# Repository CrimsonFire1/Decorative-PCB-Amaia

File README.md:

# Decorative-PCB-Amaia
 Decorative PCB powered by Arduino Nano with LEDs (3 on-off, 3 capable of dimming), two piezo buzzers (play duets), and a button. Protective back is laser cut acrylic.

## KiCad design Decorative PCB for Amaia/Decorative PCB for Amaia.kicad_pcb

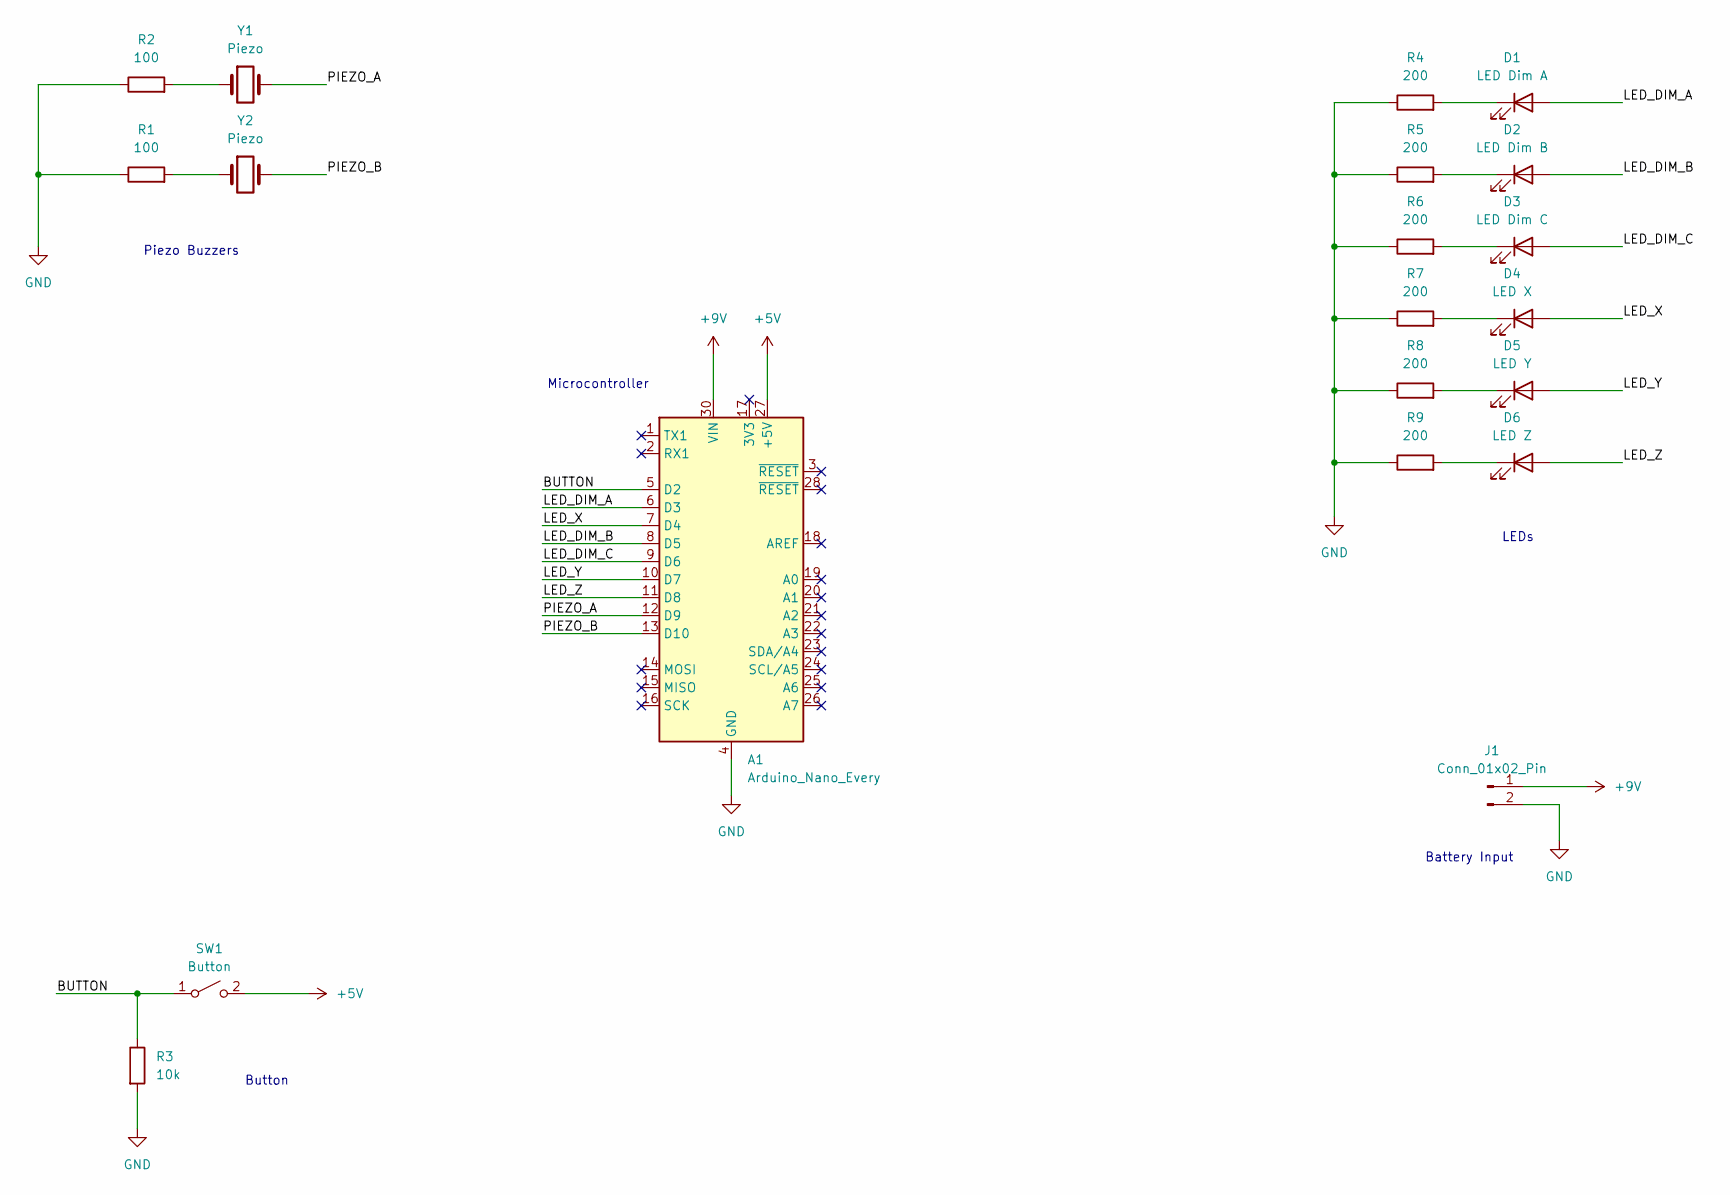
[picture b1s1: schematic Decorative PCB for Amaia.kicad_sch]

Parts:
A1: Arduino_Nano_Every; Nano_Every_Modified_Pads
D1: LED Dim A; LED_D5.0mm
D2: LED Dim B; LED_D5.0mm
D3: LED Dim C; LED_D5.0mm
D4: LED X; LED_D5.0mm
D5: LED Y; LED_D5.0mm
D6: LED Z; LED_D5.0mm
J1: Conn_01x02_Pin; SolderWire-0.5sqmm_1x02_P4.6mm_D0.9mm_OD2.1mm
R1, R2: 100; R_Axial_DIN0204_L3.6mm_D1.6mm_P7.62mm_Horizontal
R3: 10k; R_Axial_DIN0204_L3.6mm_D1.6mm_P7.62mm_Horizontal
R4, R5, R6, R7, R8, R9: 200; R_Axial_DIN0204_L3.6mm_D1.6mm_P7.62mm_Horizontal
SW1: Button; SW_PUSH_6mm
Y1, Y2: Piezo; Buzzer_Murata_PKMCS0909E

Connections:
+5V: A1.27 (+5V), SW1.2 (B)
+9V: A1.30 (VIN), J1.1
/BUTTON: A1.5 (D2), R3.1, SW1.1 (A)
/LED_DIM_A: A1.6 (D3), D1.2 (A)
/LED_DIM_B: A1.8 (D5), D2.2 (A)
/LED_DIM_C: A1.9 (D6), D3.2 (A)
/LED_X: A1.7 (D4), D4.2 (A)
/LED_Y: A1.10 (D7), D5.2 (A)
/LED_Z: A1.11 (D8), D6.2 (A)
/PIEZO_A: A1.12 (D9), Y1.2
/PIEZO_B: A1.13 (D10), Y2.2
GND: A1.4 (GND), A1.29 (GND), J1.2, R1.1, R2.1, R3.2, R4.1, R5.1, R6.1, R7.1, R8.1, R9.1
unnamed: D1.1 (K), R4.2
unnamed: D2.1 (K), R5.2
unnamed: D3.1 (K), R6.2
unnamed: D4.1 (K), R7.2
unnamed: D5.1 (K), R8.2
unnamed: D6.1 (K), R9.2
unnamed: R1.2, Y2.1
unnamed: R2.2, Y1.1

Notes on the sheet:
Battery Input
Button
Piezo Buzzers
Microcontroller
LEDs

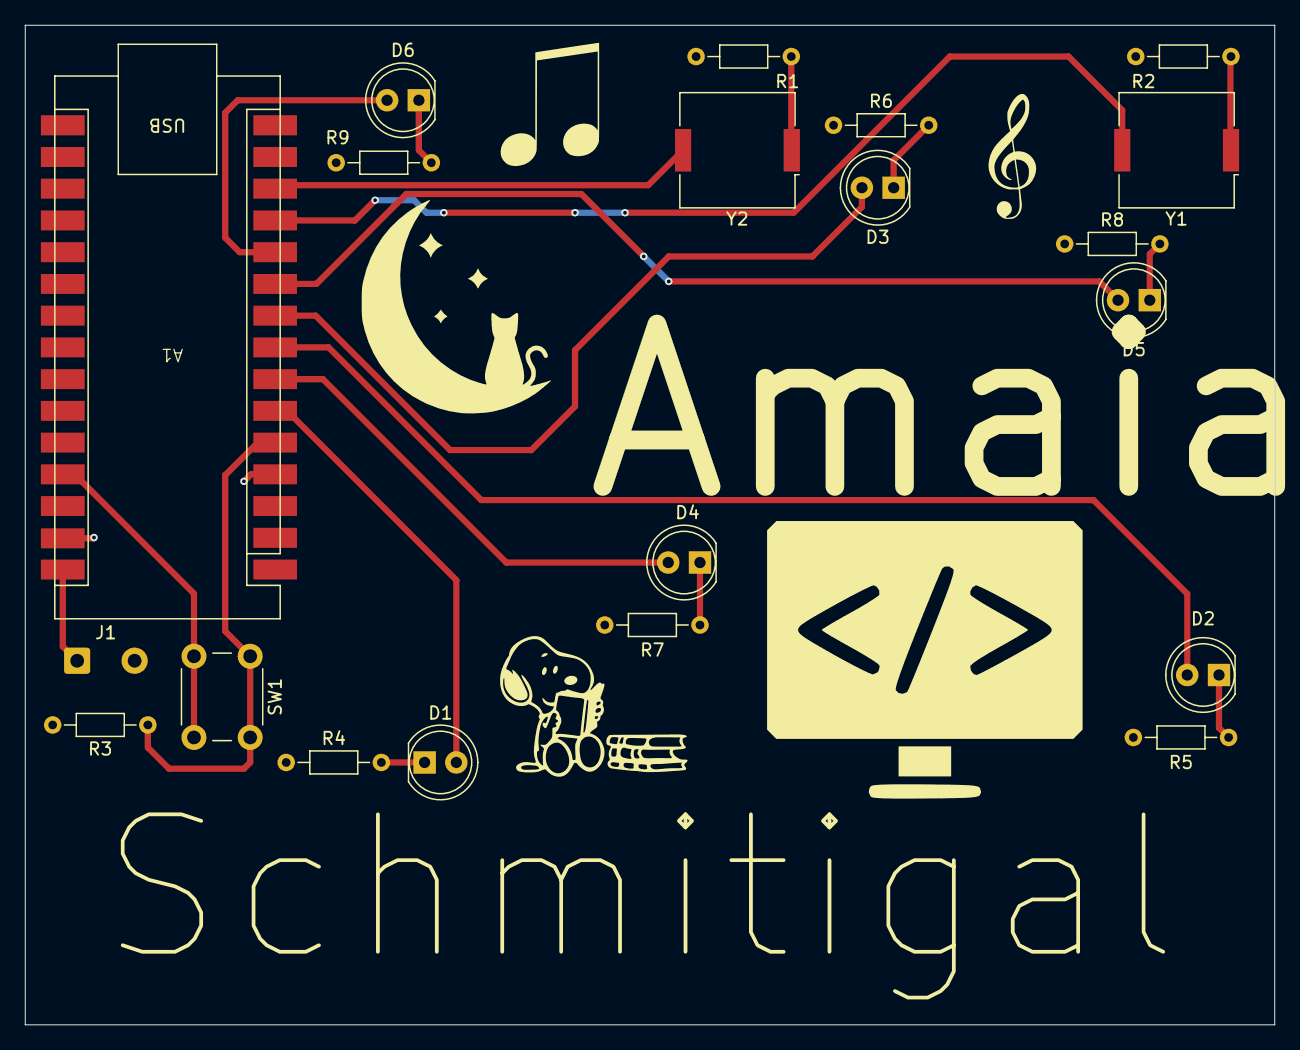
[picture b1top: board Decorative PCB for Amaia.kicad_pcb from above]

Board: 2 copper layers, 100.0 x 80.0 mm, 20 parts (0 on the bottom side), 20 nets.

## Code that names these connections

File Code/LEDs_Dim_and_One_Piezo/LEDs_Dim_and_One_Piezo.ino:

int led_brightness = 0;
bool increasing = true;

const int BUTTON = 2;

const int LED_DIM_A = 3;
const int LED_DIM_B = 5;
const int LED_DIM_C = 6;

const int LED_X = 4;
const int LED_Y = 7;
const int LED_Z = 8;

const int PIEZO_A = 9;
const int PIEZO_B = 10;

void setup()
{
  pinMode(BUTTON, INPUT);
  
  pinMode(LED_DIM_A, OUTPUT);
  pinMode(LED_DIM_B, OUTPUT);
  pinMode(LED_DIM_C, OUTPUT);
  
  pinMode(LED_X, OUTPUT);
  pinMode(LED_Y, OUTPUT);
  pinMode(LED_Z, OUTPUT);
  
  pinMode(PIEZO_A, OUTPUT);
  pinMode(PIEZO_B, OUTPUT);
  
  digitalWrite(LED_X, HIGH);
  digitalWrite(LED_Y, HIGH);
  digitalWrite(LED_Z, HIGH);
  
  Serial.begin(9600);
}

void loop()
{
  analogWrite(LED_DIM_A, led_brightness);
  analogWrite(LED_DIM_B, led_brightness);
  analogWrite(LED_DIM_C, led_brightness);
  
  if (increasing) {
    ++led_brightness;
  }
  else {
    --led_brightness;
  }
  
  if (led_brightness > 255) {
    increasing = false;
    led_brightness = 255;
  } else if (led_brightness < 0) {
    increasing = true;
    led_brightness = 0;
  }
  
  if (digitalRead(BUTTON) == HIGH) {
    delay(50);
    if (digitalRead(BUTTON) == HIGH) {
      Serial.println("here");
      playMusic();
    }
  }
  
  delay(5);
}

void playMusic() {
  digitalWrite(LED_DIM_A, HIGH);
  digitalWrite(LED_DIM_B, HIGH);
  digitalWrite(LED_DIM_C, HIGH);
  
  tone(PIEZO_A, 440);
  delay(1000);
  noTone(PIEZO_A);
  return;
}

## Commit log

2025-02-06 Added KiCad files
2025-02-06 Reorganized files, added Fab Docs and Schematic PDFs
2025-02-06 Added BOM
2025-02-09 Updated Fab docs
2025-02-09 Added basic code for Nano
    Dim LEDS go from 0 to 255. Normal LEDs stay on. Button is functional. Only one piezo works, need to use Tone.h library to enable multiple piezo simultaneous use.
2025-02-12 Added code for LEDs dimming and a button controlling LEDs
2025-02-13 Added code to test piezos
2025-02-13 Added code that plays melody, also added music for Super Mario Bros Theme and Happy Birthday
2025-02-13 Moved README
2025-02-13 Added code for Happy Birthday and lights
2025-02-13 Added pictures and video
